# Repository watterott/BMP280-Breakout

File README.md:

# BMP280-Breakout
Breakout with BMP280 Digital Absolute Barometric Pressure Sensor from Bosch Sensortec.

* [Bosch BMP280](https://www.bosch-sensortec.com/bst/products/all_products/bmp280) Absolute Barometric Pressure Sensor
* Pressure Range: 300...1100hPa (+9000...-500m above/below sea level)
* On-board 1.8V voltage regulator
* SPI Interface (up to 10MHz)
* TWI/I2C Interface (address 0x76 when SDO=0 or 0x77 when SDO=1, CS=1 for I2C)
* 3.3V - 5V Power Supply and Logic Level
* Open-Source and released under the [Creative Commons Attribution Share-Alike License](https://creativecommons.org/licenses/by-sa/4.0/).
* **[Documentation on learn.watterott.com](https://learn.watterott.com)**

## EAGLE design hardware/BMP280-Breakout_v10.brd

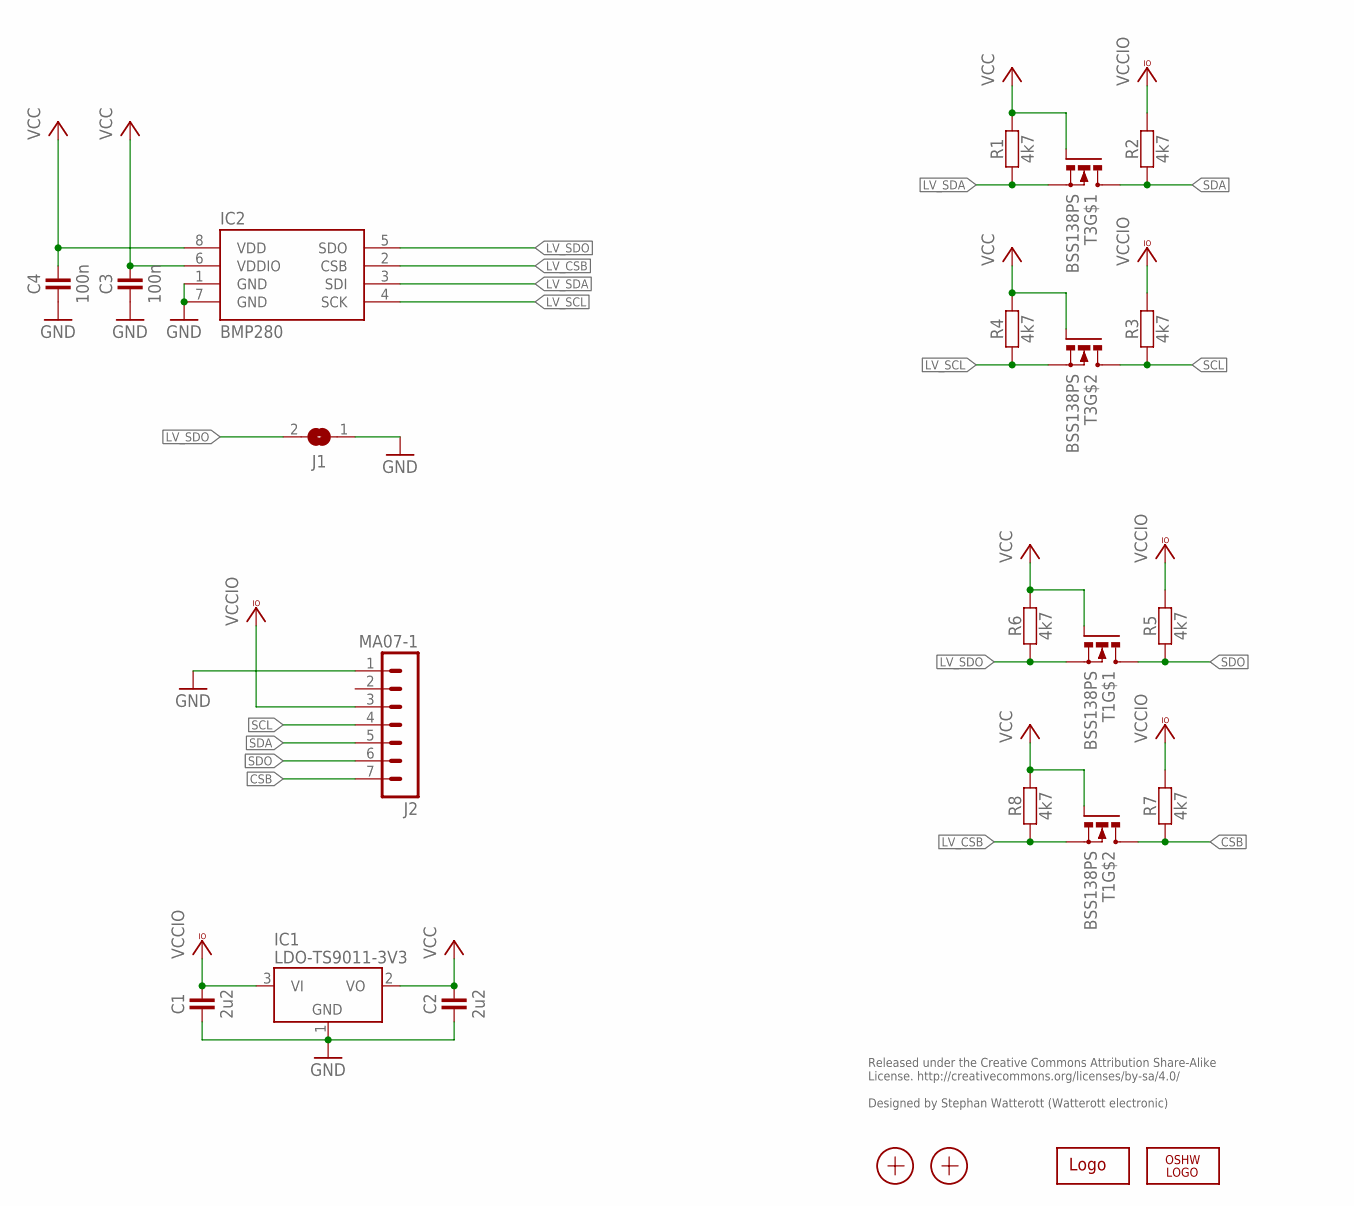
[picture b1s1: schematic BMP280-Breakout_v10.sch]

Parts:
C1, C2: 2u2; R0402
C3, C4: 100n; R0402
IC1: LDO-TS9011-3V3; SOT23
IC2: BMP280; LGA
J1: JUMPER2
J2: MA07-1
LOGO1: LOGO-S_PLACE_M; SPARK_TPLACE_M
LOGO2: OSHW_LOGOX0070; OSHW_6X70
R1, R2, R3, R4, R5, R6, R7, R8: 4k7; R0402
T1, T3: BSS138PS; SOT363
X1, X2: PASSER-07; PASSER_07MM

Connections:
CSB: J2.7, R7.1, T1.3 (D)
GND: C1.1, C2.1, C3.1, C4.1, IC1.1 (GND), IC2.1 (GND), IC2.7 (GND), J1.1, J2.1
LV_CSB: IC2.2 (CSB), R8.1, T1.4 (S)
LV_SCL: IC2.4 (SCK), R4.1, T3.4 (S)
LV_SDA: IC2.3 (SDI), R1.1, T3.1 (S)
LV_SDO: IC2.5 (SDO), J1.2, R6.1, T1.1 (S)
SCL: J2.4, R3.1, T3.3 (D)
SDA: J2.5, R2.1, T3.6 (D)
SDO: J2.6, R5.1, T1.6 (D)
VCC: C2.2, C3.2, C4.2, IC1.2 (VO), IC2.6 (VDDIO), IC2.8 (VDD), R1.2, R4.2, R6.2, R8.2, T1.2 (G), T1.5 (G), T3.2 (G), T3.5 (G)
VCCIO: C1.2, IC1.3 (VI), J2.3, R2.2, R3.2, R5.2, R7.2

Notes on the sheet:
Released under the Creative Commons Attribution Share-Alike License. http://creativecommons.org/licenses/by-sa/4.0/ Designed by Stephan Watterott (Watterott electronic)

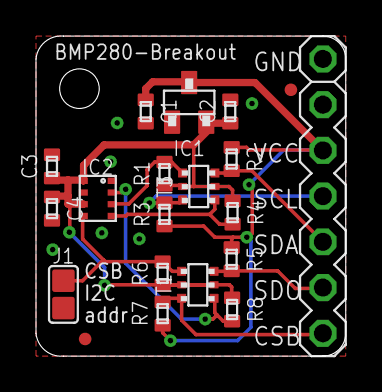
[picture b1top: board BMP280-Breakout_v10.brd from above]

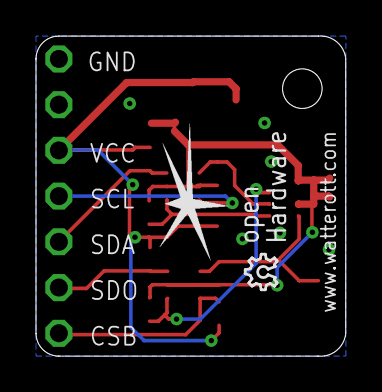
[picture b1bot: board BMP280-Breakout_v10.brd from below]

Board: 2 copper layers, 17.2 x 17.8 mm, 22 parts (2 on the bottom side), 11 nets.
